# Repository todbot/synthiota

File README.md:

# synthiota

Pico/Pico2-based board for playing with synthesizers in CircuitPython.

https://github.com/user-attachments/assets/3d1baa3f-af72-41ba-9afe-a45eea070c66

## Video demos:

- "tbish" TB-303 like synth, demo2: https://youtu.be/MjE2wdevc3M
- "tbish" TB-303 like synth, demo1: https://youtu.be/O4a5pk78DVM

# Apps

Each app's folder has a README with its controls. To install, 
find the corresponding UF2 in the [Releases](https://github.com/todbot/synthiota/releases) 
section and copy the UF2 to the board in BOOT mode. 
Or look in the app's directory for how to install it.

CircuitPython, in [`circuitpython/`](./circuitpython):

- [`polysynth`](./circuitpython/polysynth) -- two-oscillator
  subtractive polysynth. The pads are a chromatic keyboard and the pots
  edit 16 params over 2 pages.
- [`wavesynth`](./circuitpython/wavesynth) -- wavetable polysynth. The
  pads are a scale keyboard, with chords on the top row, and the pots
  edit 24 params over 3 pages.
- [`swarmsynth`](./circuitpython/swarmsynth) -- Swarmatron-style drone:
  eight oscillators on one pitch, fanned apart by the right slider.
- [`dronesynth`](./circuitpython/dronesynth) -- eight drone oscillators,
  each tuned by its own knob, each with its own LFO.
- [`dronesynth_wt`](./circuitpython/dronesynth_wt) -- dronesynth with
  each oscillator at its own place in a shared wavetable.
- [`tbish2`](./circuitpython/tbish2) -- TB-303-style acid bassline with
  a 16-step sequencer you can edit on the board.
- [`tbish`](./circuitpython/tbish) -- the original TB-303-style synth,
  a technology demo with no pattern editing or MIDI in.
- [`hwtest`](./circuitpython/hwtest) -- hardware bring-up tests and the
  reference pin setup.

Arduino, in [`arduino/`](./arduino):

- [`wavesynth`](./arduino/wavesynth) -- a Mozzi port of the
  CircuitPython wavesynth, in progress. It serves the CIRCUITPY drive
  over USB for wavetables and patches.
- [`hwtest`](./arduino/hwtest) -- a board test, plus simple mono MIDI
  synths using M16 and Mozzi.

See [Getting to BOOT mode via commandline](#getting-to-boot-mode-via-commandline)
for another way to install these apps.

# Assembling

The PCBAs come with all SMD parts assembled. The components you will need to supply:

- 1 x Raspberry Pi Pico 2
- 1 x [PCM5102 I2S Stereo DAC](https://amzn.to/4nX4xkD)
- 1 x [SH1106 128x64 1.3" SPI OLED](https://amzn.to/4oUlOeM) 
- 2 x [PJ320A 3.5mm stereo jack](https://amzn.to/4i5F33d)
- 8 x [RK09K 10k vertical potentiometer](https://amzn.to/47XbwEk) (or similar)
- 1 x [EC11 rotary encoder](https://amzn.to/4o1vSSW)
- 2 x 20-pin 5 mm "short" header socket for Pico (see below)
- 1 x 7-pin 5mm "short" header socket for display (see below)
- 8 x knobs for pots
- 1 x knob for encoder

For the knobs, you can buy knobs off Amazon or you can 3d print them.
Some 3D printable knobs I like are [these 6mm Vintage Synth Knob](https://makerworld.com/en/models/2665733-6mm-vintage-synth-knob-80s-boss-style#profileId-2949654).

### PCM5102 DAC setup

Before soldering down the PCM5102 DAC, solder bridge the jumpers 
to be 1L/2L/3H/4L, as in this picture:

The PCM5102 DAC should have standard header pins soldered to it, on the 6-pin 
header row. For extra stability, you can also solder one of the G pins behind
the audio jack.

More inforomation about the PCM5102 can be found [in this blog post](https://todbot.com/blog/2023/05/16/cheap-stereo-line-out-i2s-dac-for-circuitpython-arduino-synths/).

### Header sockets and header pins

You will also need some headers and header sockets to attach the modules to the PCB.
If using the [enclosure](./enclosure), the top part expects the header arrangement to be:

- Pico: 
  - [Short socket headers](https://www.adafruit.com/product/5585) for Pico on synthiota board
  - Standard header pins on Pico  (Pico H sold w/ these pins soldered)
- OLED display:
  - [Short socket headers](https://www.adafruit.com/product/5585) for OLED display on synthio  - Standard header pins on OLED display  (usually sold w/ these pins soldered)
ta board
- PCM5102 I2S DAC
  - Standard header pins on PCM5102 I2S DAC board (usually sold w/ these pins soldered)
  - I2S DAC w/ header pins is soldered directly to the synthiota board, no socket

When soldering down the jacks and sockets, holding them in place with masking tape
or blutack makes things easier. For the Pico header sockets, sticking them into 
a Pico and hold the Pico onto the board with masking tape or blutack can be helpful.

After soldering everything, the result will look like:

# Pico pins used

CircuitPython naming. See `hwtest/synth_setup_synthiota.py` for how they're used.

Encoder 

* `board.GP28`  - encoder B pin
* `board.GP27`  - encoder A pin

ADC input for pots

* `board.GP26`  - ADC input for pot knobs

I2S DAC 

* `board.GP22`  - I2S DAT pin to PCM5102 DAC
* `board.GP21`  - I2S LCK pin to PCM5102 DAC
* `board.GP20`  - I2S BCK pin to PCM5102 DAC

Encoder switch

* `board.GP19`  - encoder SW pin
 
NeoPixel LEDs
 
* `board.GP18`  - NeoPixel LEDs pin 
 
UART MIDI In/Out
 
* `board.GP17`  - UART RX pin to MIDI input
* `board.GP16`  - UART TX pin to MIDI output

SPI for display

* `board.GP13`  - SPI DC for SH1106 display
* `board.GP12`  - SPI RES for SH1106 display
* `board.GP11`  - SPI MOSI for SH1106 display
* `board.GP10`  - SPI SCK for SH1106 display

Pot mux select

* `board.GP9`   - SEL A pin to 4051 mux for pot knobs
* `board.GP8`   - SEL B pin to 4051 mux for pot knobs
* `board.GP7`   - SEL C pin to 4051 mux for pot knobs

I2C for MPR121 touch sensors

* `board.GP3`   - I2C SCL to MPR121 touch sensors
* `board.GP2`   - I2C SDA to MPR121 touch sensors

Free pins: GP0,GP1, GP4,GP5,GP6, GP14,GP15. Feel free to use for other purposes. 

# Schematics

## Getting to BOOT mode via commandline

If you don't want to hold the BOOT button down while powering on, 
you can usually get the synthiota board into BOOT mode via the commandline with:

```sh
PORT=/dev/cu.usbmodem21301   # the COM port of the Pico
python3 -c "import serial;serial.Serial('$PORT',1200).close()"
```

If you don't want to use Python, one of these should work:

```
stty -f $PORT 1200  # MacOS 
stty -F $PORT 1200  # Linux
```

To install a UF2 once in BOOT mode, you can do (this flashes and starts the program):

```sh
picotool load -x file.uf2
```

Or `picotool reboot` to reset board.  

(if you need, `pip3 install pyserial` and `brew install picotool`)

(note most product links are Amazon affiliate links)

https://github.com/user-attachments/assets/1fe45b23-2a2a-41f4-9afe-203840c703e8

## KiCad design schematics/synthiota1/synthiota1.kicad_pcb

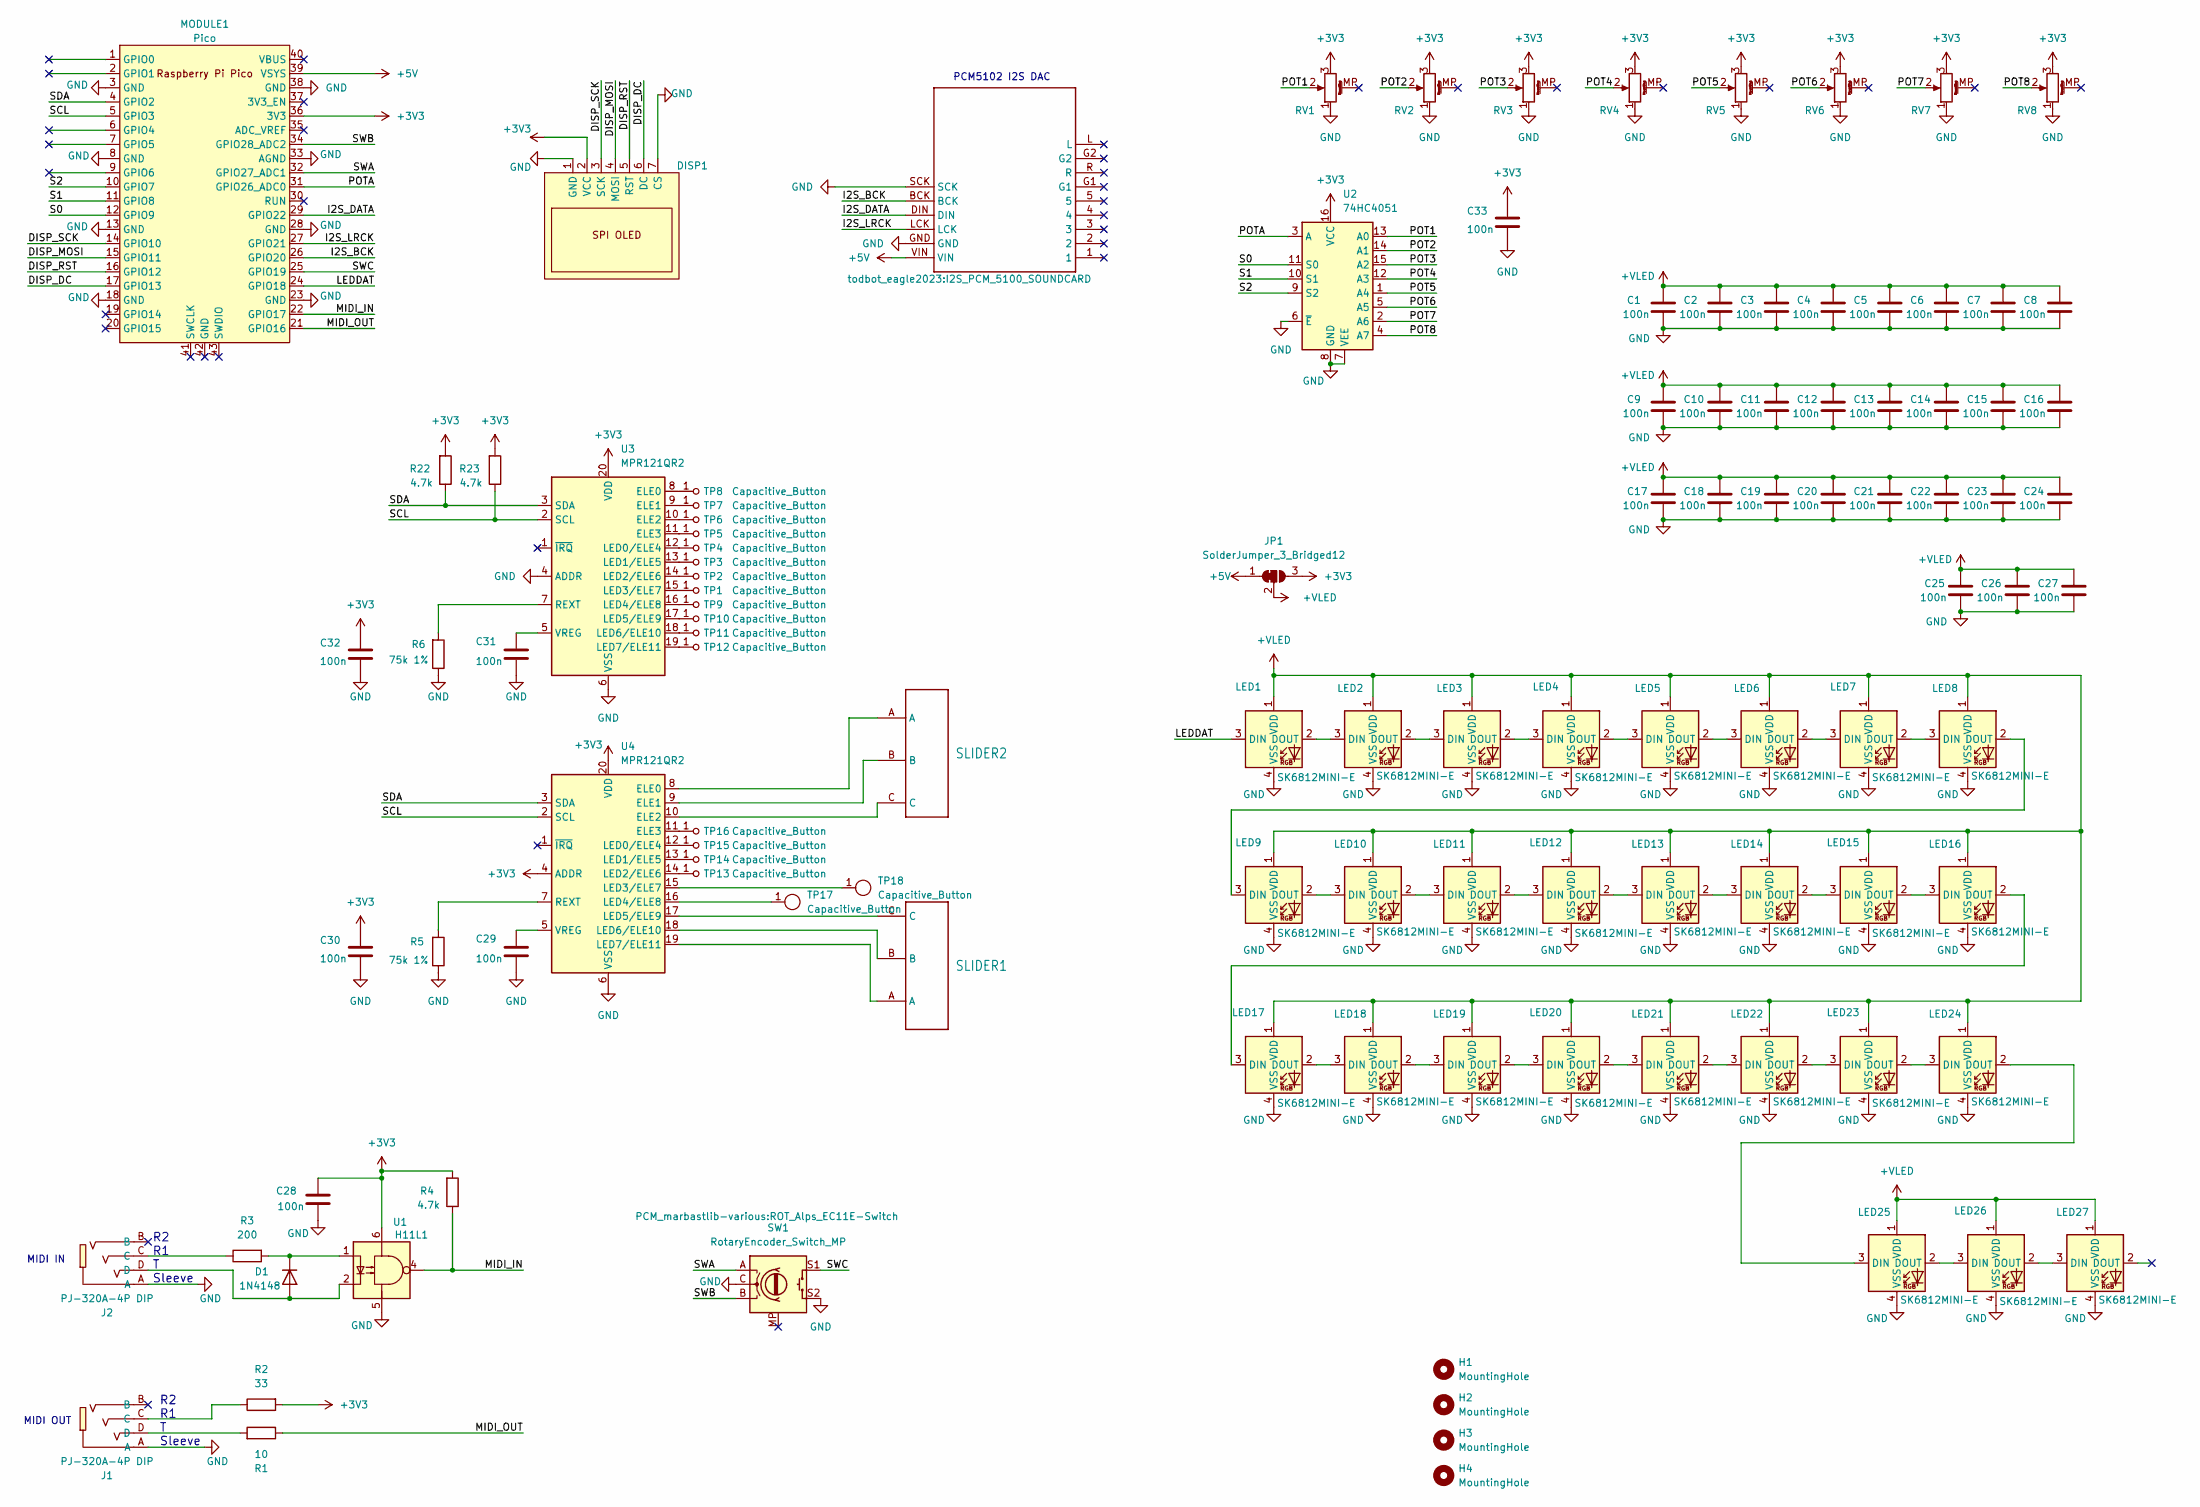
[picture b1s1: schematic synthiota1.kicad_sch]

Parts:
C1, C2, C3, C4, C5, C6, C7, C8, C9, C10, C11, C12, C13, C14, C15, C16, C17, C18, C19, C20, C21, C22, C23, C24, C25, C26, C27, C28, C29, C30, C31, C32, C33: 100n; C_0603_1608Metric; LCSC Part C1590
D1: 1N4148; D_SOD-123; LCSC Part C81598
DISP1: DISPLAY-OLED-128X64-1.3IN
H1, H2, H3, H4: MountingHole; MountingHole_2.7mm_M2.5
J1, J2: PJ-320A-4P DIP; AUDIO-TH_PJ-320A-4P-DIP; LCSC Part C18185602
JP1: SolderJumper_3_Bridged12; SolderJumper-3_P1.3mm_Bridged12_RoundedPad1.0x1.5mm
LED1, LED2, LED3, LED4, LED5, LED6, LED7, LED8, LED9, LED10, LED11, LED12, LED13, LED14, LED15, LED16, LED17, LED18, LED19, LED20, LED21, LED22, LED23, LED24, LED25, LED26, LED27: SK6812MINI-E; LED_6028R; LCSC Part C5149201
MODULE1: Pico; RPi_Pico_SMD_TH
MODULE2: I2S_PCM_5100_SOUNDCARD
R1: 10; R_0603_1608Metric; LCSC Part C22859
R2: 33; R_0603_1608Metric; LCSC Part C23140
R3: 200; R_0603_1608Metric; LCSC Part C8218
R4, R22, R23: 4.7k; R_0603_1608Metric; LCSC Part C23162
R5, R6: 75k 1%; R_0603_1608Metric; LCSC Part C23242
RV1, RV2, RV3, RV4, RV5, RV6, RV7, RV8: R_Potentiometer_MountingPin; Potentiometer_Alps_RK09K_Single_Vertical
SLIDER1, SLIDER2: TouchSlider3_50x8mm_ti
SW1: RotaryEncoder_Switch_MP; ROT_Alps_EC11E-Switch
TP1, TP2, TP3, TP4, TP5, TP6, TP7, TP8, TP9, TP10, TP11, TP12, TP13, TP14, TP15, TP16: Capacitive_Button; TOUCHPAD_KEY_0.5IN_LEDHOLE
TP17, TP18: Capacitive_Button; Pad-CapTouch-8mm-roundrect
U1: H11L1; SMD-6_L7.3-W6.5-P2.54-LS10.2-BL; LCSC C78589
U2: 74HC4051; SOIC-16_L9.9-W3.9-P1.27-LS6.0-BL; LCSC Part C2943297
U3, U4: MPR121QR2; UQFN-20_3x3mm_P0.4mm; LCSC Part C91322

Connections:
+3V3: C28.1, C30.1, C32.1, C33.1, DISP1.2 (VCC), JP1.3 (B), MODULE1.36 (3V3), R2.2, R4.2, R22.2, R23.2, RV1.3, RV2.3, RV3.3, RV4.3, RV5.3, RV6.3, RV7.3, RV8.3, U1.6, U2.16 (VCC), U3.20 (VDD), U4.4 (ADDR), U4.20 (VDD)
+5V: JP1.1 (A), MODULE1.39 (VSYS), MODULE2.VIN
+VLED: C1.1, C2.1, C3.1, C4.1, C5.1, C6.1, C7.1, C8.1, C9.1, C10.1, C11.1, C12.1, C13.1, C14.1, C15.1, C16.1, C17.1, C18.1, C19.1, C20.1, C21.1, C22.1, C23.1, C24.1, C25.1, C26.1, C27.1, JP1.2 (C), LED1.1 (VDD), LED2.1 (VDD), LED3.1 (VDD), LED4.1 (VDD), LED5.1 (VDD), LED6.1 (VDD), LED7.1 (VDD), LED8.1 (VDD), LED9.1 (VDD), LED10.1 (VDD), LED11.1 (VDD), LED12.1 (VDD), LED13.1 (VDD), LED14.1 (VDD), LED15.1 (VDD), LED16.1 (VDD), LED17.1 (VDD), LED18.1 (VDD), LED19.1 (VDD), LED20.1 (VDD), LED21.1 (VDD), LED22.1 (VDD), LED23.1 (VDD), LED24.1 (VDD), LED25.1 (VDD), LED26.1 (VDD), LED27.1 (VDD)
/DISP_DC: DISP1.6 (DC), MODULE1.17 (GPIO13)
/DISP_MOSI: DISP1.4 (MOSI), MODULE1.15 (GPIO11)
/DISP_RST: DISP1.5 (RST), MODULE1.16 (GPIO12)
/DISP_SCK: DISP1.3 (SCK), MODULE1.14 (GPIO10)
/I2S_BCK: MODULE1.26 (GPIO20), MODULE2.BCK
/I2S_DATA: MODULE1.29 (GPIO22), MODULE2.DIN
/I2S_LRCK: MODULE1.27 (GPIO21), MODULE2.LCK
/LEDDAT: LED1.3 (DIN), MODULE1.24 (GPIO18)
/MIDI_IN: MODULE1.22 (GPIO17), R4.1, U1.4
/MIDI_OUT: MODULE1.21 (GPIO16), R1.1
/POT1: RV1.2, U2.13 (A0)
/POT2: RV2.2, U2.14 (A1)
/POT3: RV3.2, U2.15 (A2)
/POT4: RV4.2, U2.12 (A3)
/POT5: RV5.2, U2.1 (A4)
/POT6: RV6.2, U2.5 (A5)
/POT7: RV7.2, U2.2 (A6)
/POT8: RV8.2, U2.4 (A7)
/POTA: MODULE1.31 (GPIO26_ADC0), U2.3 (A)
/S0: MODULE1.12 (GPIO9), U2.11 (S0)
/S1: MODULE1.11 (GPIO8), U2.10 (S1)
/S2: MODULE1.10 (GPIO7), U2.9 (S2)
/SCL: MODULE1.5 (GPIO3), R23.1, U3.2 (SCL), U4.2 (SCL)
/SDA: MODULE1.4 (GPIO2), R22.1, U3.3 (SDA), U4.3 (SDA)
/SWA: MODULE1.32 (GPIO27_ADC1), SW1.A
/SWB: MODULE1.34 (GPIO28_ADC2), SW1.B
/SWC: MODULE1.25 (GPIO19), SW1.S1
GND: C1.2, C2.2, C3.2, C4.2, C5.2, C6.2, C7.2, C8.2, C9.2, C10.2, C11.2, C12.2, C13.2, C14.2, C15.2, C16.2, C17.2, C18.2, C19.2, C20.2, C21.2, C22.2, C23.2, C24.2, C25.2, C26.2, C27.2, C28.2, C29.2, C30.2, C31.2, C32.2, C33.2, DISP1.1 (GND), DISP1.7 (CS), J1.A, J2.A, LED1.4 (VSS), LED2.4 (VSS), LED3.4 (VSS), LED4.4 (VSS), LED5.4 (VSS), LED6.4 (VSS), LED7.4 (VSS), LED8.4 (VSS), LED9.4 (VSS), LED10.4 (VSS), LED11.4 (VSS), LED12.4 (VSS), LED13.4 (VSS), LED14.4 (VSS), LED15.4 (VSS), LED16.4 (VSS), LED17.4 (VSS), LED18.4 (VSS), LED19.4 (VSS), LED20.4 (VSS), LED21.4 (VSS), LED22.4 (VSS), LED23.4 (VSS), LED24.4 (VSS), LED25.4 (VSS), LED26.4 (VSS), LED27.4 (VSS), MODULE1.3 (GND), MODULE1.8 (GND), MODULE1.13 (GND), MODULE1.18 (GND), MODULE1.23 (GND), MODULE1.28 (GND), MODULE1.33 (AGND), MODULE1.38 (GND), MODULE2.GND, MODULE2.SCK, R5.1, R6.1, RV1.1, RV2.1, RV3.1, RV4.1, RV5.1, RV6.1, RV7.1, RV8.1, SW1.C, SW1.S2, U1.5, U2.6 (~E), U2.7 (VEE), U2.8 (GND), U3.4 (ADDR), U3.6 (VSS), U4.6 (VSS)
unnamed: D1.2 (A), J2.D, U1.2
unnamed: D1.1 (K), R3.2, U1.1
unnamed: J1.C, R2.1
unnamed: J1.D, R1.2
unnamed: J2.C, R3.1
unnamed: LED1.2 (DOUT), LED2.3 (DIN)
unnamed: LED2.2 (DOUT), LED3.3 (DIN)
unnamed: LED3.2 (DOUT), LED4.3 (DIN)
unnamed: LED4.2 (DOUT), LED5.3 (DIN)
unnamed: LED5.2 (DOUT), LED6.3 (DIN)
unnamed: LED6.2 (DOUT), LED7.3 (DIN)
unnamed: LED7.2 (DOUT), LED8.3 (DIN)
unnamed: LED8.2 (DOUT), LED9.3 (DIN)
unnamed: LED9.2 (DOUT), LED10.3 (DIN)
unnamed: LED10.2 (DOUT), LED11.3 (DIN)
unnamed: LED11.2 (DOUT), LED12.3 (DIN)
unnamed: LED12.2 (DOUT), LED13.3 (DIN)
unnamed: LED13.2 (DOUT), LED14.3 (DIN)
unnamed: LED14.2 (DOUT), LED15.3 (DIN)
unnamed: LED15.2 (DOUT), LED16.3 (DIN)
unnamed: LED16.2 (DOUT), LED17.3 (DIN)
unnamed: LED17.2 (DOUT), LED18.3 (DIN)
unnamed: LED18.2 (DOUT), LED19.3 (DIN)
unnamed: LED19.2 (DOUT), LED20.3 (DIN)
unnamed: LED20.2 (DOUT), LED21.3 (DIN)
unnamed: LED21.2 (DOUT), LED22.3 (DIN)
unnamed: LED22.2 (DOUT), LED23.3 (DIN)
unnamed: LED23.2 (DOUT), LED24.3 (DIN)
unnamed: LED24.2 (DOUT), LED25.3 (DIN)
unnamed: LED25.2 (DOUT), LED26.3 (DIN)
unnamed: LED26.2 (DOUT), LED27.3 (DIN)
unnamed: TP1.1 (A), U3.15 (LED3/ELE7)
unnamed: TP2.1 (A), U3.14 (LED2/ELE6)
unnamed: TP3.1 (A), U3.13 (LED1/ELE5)
unnamed: TP4.1 (A), U3.12 (LED0/ELE4)
unnamed: TP5.1 (A), U3.11 (ELE3)
unnamed: TP6.1 (A), U3.10 (ELE2)
unnamed: TP7.1 (A), U3.9 (ELE1)
unnamed: TP8.1 (A), U3.8 (ELE0)
unnamed: TP9.1 (A), U3.16 (LED4/ELE8)
unnamed: TP10.1 (A), U3.17 (LED5/ELE9)
unnamed: TP11.1 (A), U3.18 (LED6/ELE10)
unnamed: TP12.1 (A), U3.19 (LED7/ELE11)
unnamed: TP13.1 (A), U4.14 (LED2/ELE6)
unnamed: TP14.1 (A), U4.13 (LED1/ELE5)
unnamed: TP15.1 (A), U4.12 (LED0/ELE4)
unnamed: TP16.1 (A), U4.11 (ELE3)
unnamed: TP17.1 (A), U4.16 (LED4/ELE8)
unnamed: TP18.1 (A), U4.15 (LED3/ELE7)
unnamed: R6.2, U3.7 (REXT)
unnamed: C31.1, U3.5 (VREG)
unnamed: SLIDER2.A, U4.8 (ELE0)
unnamed: SLIDER2.B, U4.9 (ELE1)
unnamed: SLIDER2.C, U4.10 (ELE2)
unnamed: SLIDER1.C, U4.17 (LED5/ELE9)
unnamed: SLIDER1.B, U4.18 (LED6/ELE10)
unnamed: SLIDER1.A, U4.19 (LED7/ELE11)
unnamed: R5.2, U4.7 (REXT)
unnamed: C29.1, U4.5 (VREG)

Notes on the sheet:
MIDI IN
PCM5102 I2S DAC
R2 R1 T Sleeve
MIDI OUT

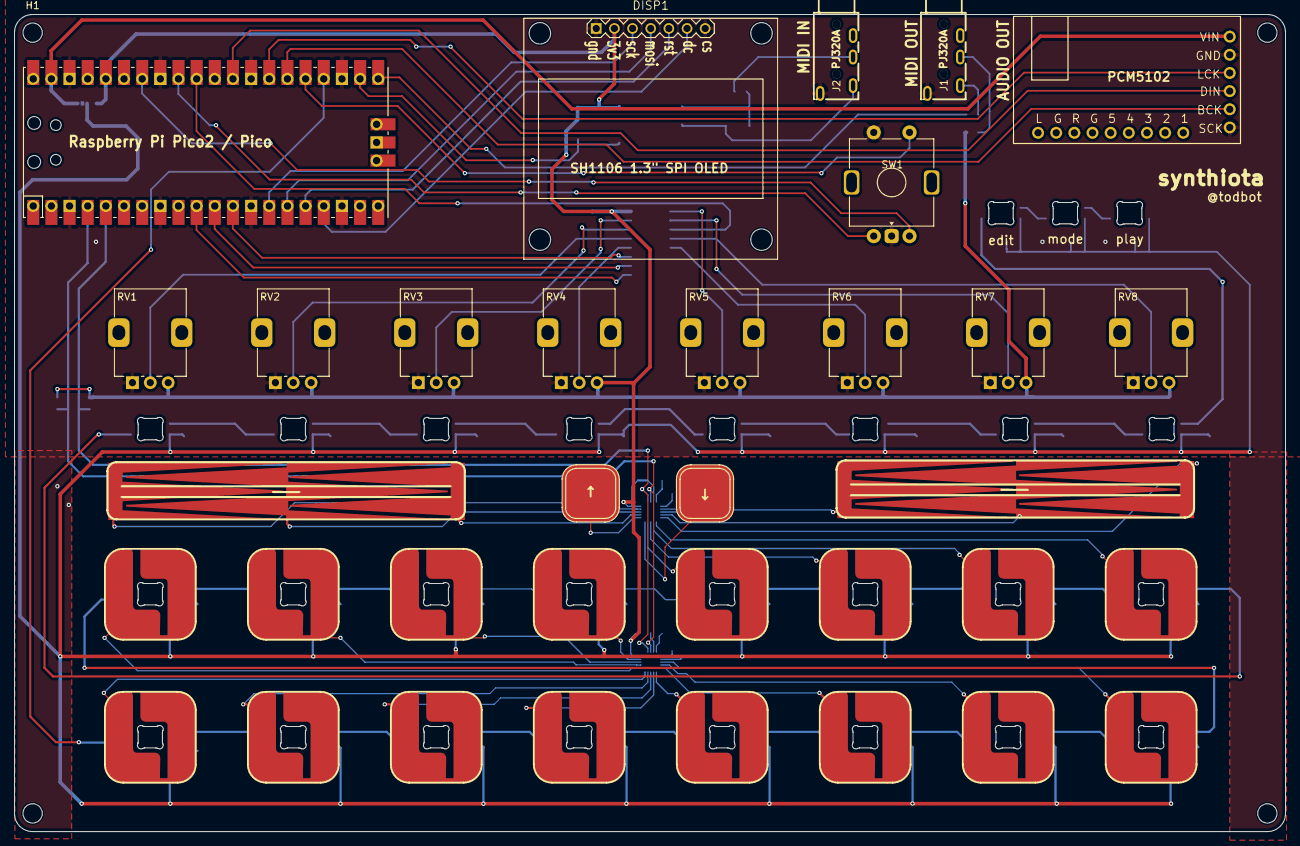
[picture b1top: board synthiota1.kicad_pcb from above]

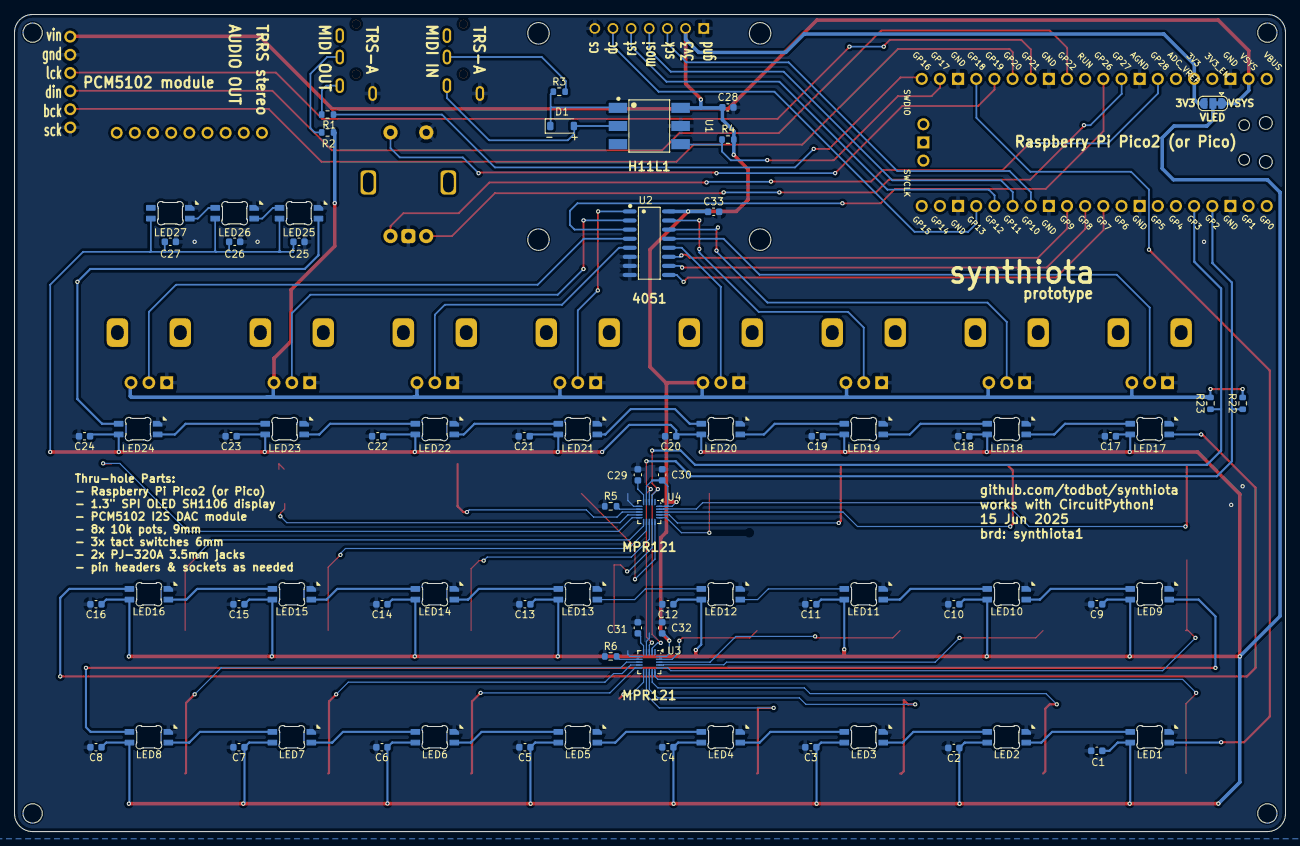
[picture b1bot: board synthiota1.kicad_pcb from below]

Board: 2 copper layers, 177.8 x 114.3 mm, 112 parts (74 on the bottom side), 90 nets.

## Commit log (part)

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2025-06-22 finally check in sch and brd, rename to synthiota from pico_touchytouchy_synth
2025-06-22 some test scripts
2025-06-22 some renders
2025-06-27 pcb cleanup
2025-06-27 pcb tweaks
2025-06-27 lcsc part nums for everything because jlc sucks now, pcb cleanup
2025-06-27 added up/dn buttons! and more pcb tweaks
2025-07-09 rotary encoder instead
2025-07-09 moved pico numbers to back haha
2025-07-09 as submitted to jlcpcb fab
2025-07-17 remove unused 3d models from footprints
2025-07-17 28M step file, no thank you
2025-07-20 add new render
2025-11-12 Enhance README with project description and images
    Added a brief description and image references for the synthiota project.
2025-11-19 assembly directions start
2025-11-19 synthest1
2025-11-19 synthtest1 fakey sequencer
2025-11-19 add enclosure
2025-11-19 sync with local
2025-12-15 fix spi oled link
2025-12-18 add requirements.txt for circuitpython examples
2025-12-22 reworked synthtest
2025-12-22 synthtest fixes
2025-12-22 forgot setup module
2026-02-03 first port of tbish from pico_test_synth to synthiota, not finished yet
2026-02-04 add english to links
2026-02-04 okay tbish working enough to show a little
2026-02-04 add sch pdf
2026-02-04 update tbish readme with new youtube link
2026-02-05 minor fixes for fun
2026-02-11 trying out a new pot control strategy
2026-02-12 make work on RP2040 maybe
2026-02-12 fix mapped_pot_controller options and reduce spurious update events
2026-02-12 tbish_synth: make work easier on rp2040
2026-02-12 synth_setup_synthiota: create synthetic events for touchpads
2026-02-12 tbish_sequencer: return before callbacks if not playing
2026-02-12 tbish: finally doing something with LEDs
2026-02-13 synth_setup_synthiota: added simple integer pot smoothing, changed tiny button MPR121 sensitivity to be less twitchy
2026-02-13 tbish: add more ui
2026-02-13 tbish synth: fix amp decay
2026-02-14 tbish: can edit steps, sequences now have separate slide track
2026-02-14 tbish: oops broke accent, fixed
2026-02-15 tbish: now change bpm and steps_per_beat by holding pad and turning encoder
2026-02-15 readme: add youtube links
